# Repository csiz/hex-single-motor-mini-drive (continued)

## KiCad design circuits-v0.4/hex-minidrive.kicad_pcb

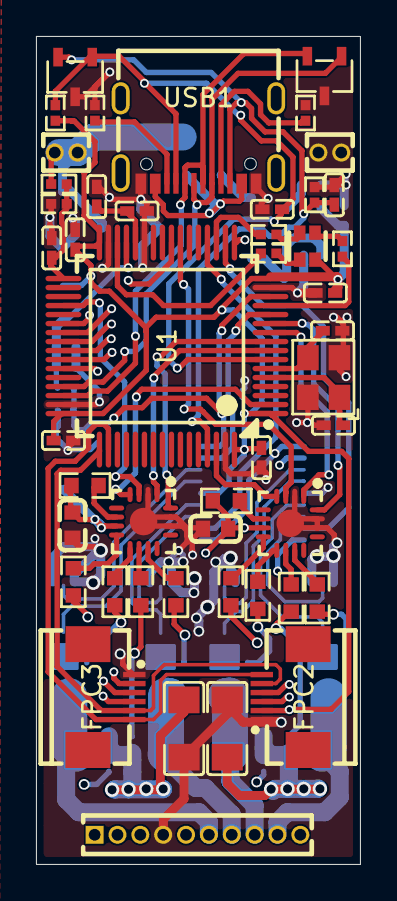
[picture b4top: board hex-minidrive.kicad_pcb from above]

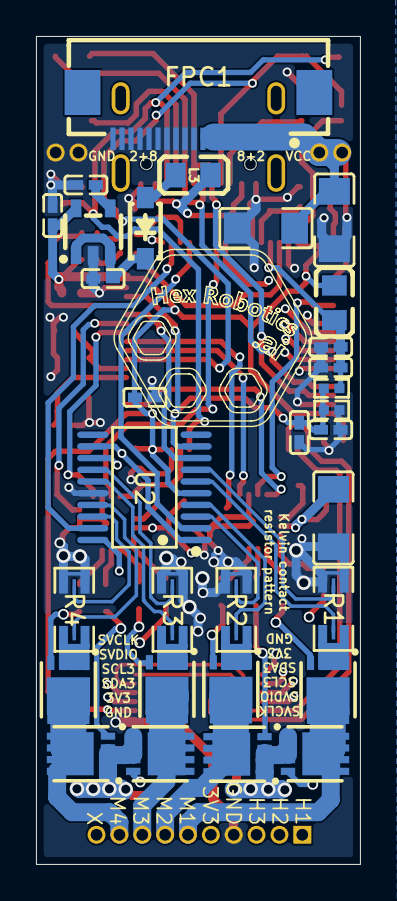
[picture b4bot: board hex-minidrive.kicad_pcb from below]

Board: 4 copper layers, 18.0 x 46.0 mm, 78 parts (31 on the bottom side), 80 nets.

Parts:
C0, C1, C2, C3, C4: 10uF; C1206
C21, C101, C106, C108, C109, C110, C111, C112, C113, C114: 100nF; C0402
C31, C32, C102, C105, C107: 1uF; C0402
C33: 10nF; C0402
C103, C104: 15pF; C0402
C115: 1nF; C0402
C501, C601: 100nF; C0603
D1: SOD-123_L2.7-W1.6-LS3.7-RD-1
D2, D3: SOT-23-3_L3.0-W1.7-P0.95-LS2.9-BR
FPC1: FPC-SMD_20P-P0.50_XUNPU_FPC-05F-20PH20
FPC2, FPC3: FPC-SMD_6P-P0.50_XUNPU_FPC-05F-6PH20
H1: 10P 1.27mm header; HDR-TH_HX-PZ1.27-1X10P-ZZ
H2, H3: 2P-1.27mm-header; HDR-TH_2P-P1.27-V-M-2
L2: 10uH; L0805
L3: 300mΩ; L0805
LED1: LED-ARRAY-SMD_4P-L1.6-W1.5-BR_XL-1615RGBC-RF
Q1, Q3, Q5, Q7: DFN-8_L3.0-W3.0-P0.65-BL-MOSFET_shifted
Q2, Q4, Q6, Q8: DFN-8_L3.0-W3.0-P0.65-BL-MOSFET
R1, R2, R3, R4: 10mΩ; R1206 Shunt with Kelvin connections
R5, R6: 5.1kΩ; R0402
R11, R12, R13, R14, R19: 10kΩ; R0402
R15, R16, R17: 1.5kΩ; R0402
R18: 100kΩ; R0402
R101, R102, R201, R202, R301, R302, R401, R402: 4.7Ω; R0603
R501, R601: 10Ω; R0603
U1: LQFP-64_L10.0-W10.0-P0.50-LS12.0-BL
U2: TSSOP-20_L6.5-W4.4-P0.65-LS6.4-BL
U3: SOT-23-5_L3.0-W1.6-P0.95-LS2.8-BL
U5, U6: QFN-16_L3.0-W3.0-P0.50-TL-EP1.7
USB1: USB-C-SMD_TYPE-C16PIN
X1: 16MHz; OSC-SMD_4P-L3.2-W2.5-BL

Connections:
3V3: C21.2, C32.2, C109.2, C111.2, C112.2, C113.2, FPC2.2, FPC3.2, H1.5, L2.1, LED1.2 (COM+), R14.1, U1.1 (VBAT), U1.16 (VDD), U1.32 (VDD), U1.48 (VDD), U1.64 (VDD), U2.5 (VS), U3.5 (OUT)
3V3A: C101.2, C102.2, L2.2, R13.2, U1.29 (VDDA)
5V: C31.2, D1.1 (-), U3.1 (IN), U3.3 (EN)
+Probe-1: R1.3 (Probe-1), U2.6 (IN+2)
+Probe-2: R2.3 (Probe-1), U2.4 (IN+1)
+Probe-3: R3.3 (Probe-1), U2.15 (IN+3)
+Probe-4: R4.3 (Probe-1), U2.17 (IN+4)
-Probe-1: R1.4 (Probe-2), U2.7 (IN±2)
-Probe-2: R2.4 (Probe-2), U2.3 (IN±1)
-Probe-3: R3.4 (Probe-2), U2.14 (IN±3)
-Probe-4: R4.4 (Probe-2), U2.18 (IN±4)
/Blue-LED: LED1.3 (B-), R16.1
/Driver1-internal-LDO: R501.2, U5.6 (VCC1)
/Driver2-internal-LDO: R601.2, U6.6 (VCC1)
/Gate-1-Negative: Q1.2 (G), R101.2
/Gate-1-Positive: Q2.2 (G), R102.1
/Gate-2-Negative: Q3.2 (G), R201.2
/Gate-2-Positive: Q4.2 (G), R202.1
/Gate-3-Negative: Q5.2 (G), R301.2
/Gate-3-Positive: Q6.2 (G), R302.1
/Gate-4-Negative: Q7.2 (G), R401.2
/Gate-4-Positive: Q8.2 (G), R402.1
/Green-LED: LED1.4 (G-), R15.1
/LDO-Bypass-Capacitor: C33.2, U3.4 (BYP)
/OSC1: C103.2, U1.5 (PF0-OSC_IN), X1.1 (OSC1)
/OSC2: C104.2, U1.6 (PF1-OSC_OUT), X1.3 (OSC2)
/Red-LED: LED1.1 (R-), R17.2
/Shunt-1: Q1.1 (S), R1.1 (Shunt-1)
/Shunt-2: Q3.1 (S), R2.1 (Shunt-1)
/Shunt-3: Q5.1 (S), R3.1 (Shunt-1)
/Shunt-4: Q7.1 (S), R4.1 (Shunt-1)
/USB:5V: L3.1, USB1.A4B9 (VBUS), USB1.B4A9 (VBUS)
/USB:5V-filtered: D1.2 (+), L3.2
/USB:CC1: R6.2, USB1.A5 (CC1)
/USB:CC2: R5.2, USB1.B5 (CC2)
ADC1_IN1/M1_CURRENT: U1.12 (PA0), U2.8 (OUT2)
ADC1_IN3/HALF_VREF: C107.2, C108.2, R12.2, R13.1, U1.14 (PA2), U2.1 (REF1), U2.9 (REF2), U2.12 (REF3), U2.20 (REF4)
ADC1_IN4/M3_CURRENT: U1.17 (PA3), U2.13 (OUT3)
ADC2_IN3/M2_CURRENT: U1.20 (PA6), U2.2 (OUT1)
ADC2_IN14/VOLTAGE: C115.2, R18.1, R19.2, U1.33 (PB11)
ADC2_IN17/M4_CURRENT: U1.18 (PA4), U2.19 (OUT4)
BOOT0/STOP: C114.2, D3.2 (A1), R11.2, U1.61 (PB8-BOOT0), USB1.B8 (SBU2)
GND: C0.1, C1.1, C2.1, C3.1, C4.1, C21.1, C31.1, C32.1, C33.1, C101.1, C102.1, C103.1, C104.1, C105.1, C106.1, C107.1, C108.1, C109.1, C110.1, C111.1, C112.1, C113.1, C114.1, C115.1, C501.1, C601.1, D2.3 (K), D3.3 (K), FPC1.11, FPC1.12, FPC1.13, FPC1.14, FPC1.15, FPC1.16, FPC1.17, FPC1.18, FPC1.19, FPC1.20, FPC2.1, FPC3.1, H1.4, H2.1, H2.2, R1.2 (Shunt-2), R2.2 (Shunt-2), R3.2 (Shunt-2), R4.2 (Shunt-2), R5.1, R6.1, R11.1, R12.1, R19.1, U1.15 (VSS), U1.27 (VSSA), U1.31 (VSS), U1.47 (VSS), U1.63 (VSS), U2.16 (GND), U3.2 (GND), U5.2 (LIN3), U5.14 (GND), U5.15 (HIN3), U5.17 (EP), U6.2 (LIN3), U6.14 (GND), U6.15 (HIN3), U6.17 (EP), USB1.A1B12 (GND), USB1.B1A12 (GND), X1.2 (GND), X1.4 (GND)
I2C2_SCL: FPC2.4, U1.43 (PA9)
I2C2_SDA: FPC2.3, U1.42 (PA8)
I2C3_SCL: FPC3.4, U1.40 (PC8)
I2C3_SDA: FPC3.3, U1.41 (PC9)
M1: H1.6, Q1.3 (D), Q2.3 (D)
M2: H1.7, Q3.3 (D), Q4.3 (D)
M3: H1.8, Q5.3 (D), Q6.3 (D)
M4: H1.9, Q7.3 (D), Q8.3 (D)
N-Gate-1: R101.1, U5.9 (LO1)
N-Gate-2: R201.1, U5.11 (LO2)
N-Gate-3: R301.1, U6.9 (LO1)
N-Gate-4: R401.1, U6.11 (LO2)
NRST: C110.2, D3.1 (A1), R14.2, U1.7 (PG10-NRST), USB1.A8 (SBU1)
P-Gate-1: R102.2, U5.8 (HO1)
P-Gate-2: R202.2, U5.10 (HO2)
P-Gate-3: R302.2, U6.8 (HO1)
P-Gate-4: R402.2, U6.10 (HO2)
SYS_JTCK-SWCLK: FPC2.6, FPC3.6, U1.50 (PA14)
SYS_JTMS-SVDIO: FPC2.5, FPC3.5, U1.49 (PA13)
TIM1_CH1: U1.8 (PC0), U5.1 (HIN1)
TIM1_CH1N: U1.2 (PC13), U5.4 (LIN1)
TIM1_CH2: U1.9 (PC1), U5.16 (HIN2)
TIM1_CH2N: U1.36 (PB14), U5.3 (LIN2)
TIM1_CH3: U1.10 (PC2), U6.1 (HIN1)
TIM1_CH3N: U1.62 (PB9), U6.4 (LIN1)
TIM1_CH4: U1.11 (PC3), U6.16 (HIN2)
TIM1_CH4N: U1.23 (PC5), U6.3 (LIN2)
TIM2_CH1/GREEN_LED: R15.2, U1.19 (PA5)
TIM2_CH2/BLUE_LED: R16.2, U1.13 (PA1)
TIM2_CH3/RED_LED: R17.1, U1.30 (PB10)
TIM3_CH1/ENCODER_1: H1.1, U1.38 (PC6)
TIM3_CH2/ENCODER_2: H1.2, U1.39 (PC7)
TIM3_CH3/ENCODER_3: H1.3, U1.24 (PB0)
USB_D_N: D2.1 (A1), U1.45 (PA11), USB1.A7 (DN1), USB1.B7 (DN2)
USB_D_P: D2.2 (A1), U1.46 (PA12), USB1.A6 (DP1), USB1.B6 (DP2)
VCC: C0.2, C1.2, C2.2, C3.2, C4.2, C501.2, C601.2, FPC1.1, FPC1.2, FPC1.3, FPC1.4, FPC1.5, FPC1.6, FPC1.7, FPC1.8, FPC1.9, FPC1.10, H3.1, H3.2, Q2.1 (S), Q4.1 (S), Q6.1 (S), Q8.1 (S), R18.2, R501.1, R601.1, U5.7 (VCC2), U6.7 (VCC2)
VREF: C105.2, C106.2, U1.28 (VREF+)

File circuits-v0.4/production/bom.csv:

Designator,Footprint,Quantity,Value,LCSC Part #
"C0, C1, C2, C3, C4",C1206,5,10uF,C13585
"C101, C106, C108, C109, C110, C111, C112, C113, C114, C21",C0402,10,100nF,C307331
"C102, C105, C107, C31, C32",C0402,5,1uF,C52923
"C103, C104",C0402,2,15pF,C1548
C115,C0402,1,1nF,C1523
C33,C0402,1,10nF,C15195
"C501, C601",C0603,2,100nF,C14663
D1,SOD-123_L2.7-W1.6-LS3.7-RD-1,1,~,C8598
"D2, D3",SOT-23-3_L3.0-W1.7-P0.95-LS2.9-BR,2,~,C32677
FPC1,FPC-SMD_20P-P0.50_XUNPU_FPC-05F-20PH20,1,~,C2856803
"FPC2, FPC3",FPC-SMD_6P-P0.50_XUNPU_FPC-05F-6PH20,2,~,C2856796
L2,L0805,1,10uH,C1046
L3,L0805,1,300mΩ,C1017
LED1,LED-ARRAY-SMD_4P-L1.6-W1.5-BR_XL-1615RGBC-RF,1,~,C965840
"Q1, Q3, Q5, Q7",DFN-8_L3.0-W3.0-P0.65-BL-MOSFET_shifted,4,~,C315567
"Q2, Q4, Q6, Q8",DFN-8_L3.0-W3.0-P0.65-BL-MOSFET,4,~,C541711
"R1, R2, R3, R4",R1206 Shunt with Kelvin connections,4,10mΩ,C7467248
"R101, R102, R201, R202, R301, R302, R401, R402",R0603,8,4.7Ω,C23164
"R11, R12, R13, R14, R19",R0402,5,10kΩ,C25744
"R15, R16, R17",R0402,3,1.5kΩ,C25867
R18,R0402,1,100kΩ,C25741
"R5, R6",R0402,2,5.1kΩ,C25905
"R501, R601",R0603,2,10Ω,C22859
U1,LQFP-64_L10.0-W10.0-P0.50-LS12.0-BL,1,~,C431633
U2,TSSOP-20_L6.5-W4.4-P0.65-LS6.4-BL,1,~,C2058366
U3,SOT-23-5_L3.0-W1.6-P0.95-LS2.8-BL,1,~,C2969807
"U5, U6",QFN-16_L3.0-W3.0-P0.50-TL-EP1.7,2,~,C20416138
USB1,USB-C-SMD_TYPE-C16PIN,1,~,C393939
X1,OSC-SMD_4P-L3.2-W2.5-BL,1,16MHz,C13738

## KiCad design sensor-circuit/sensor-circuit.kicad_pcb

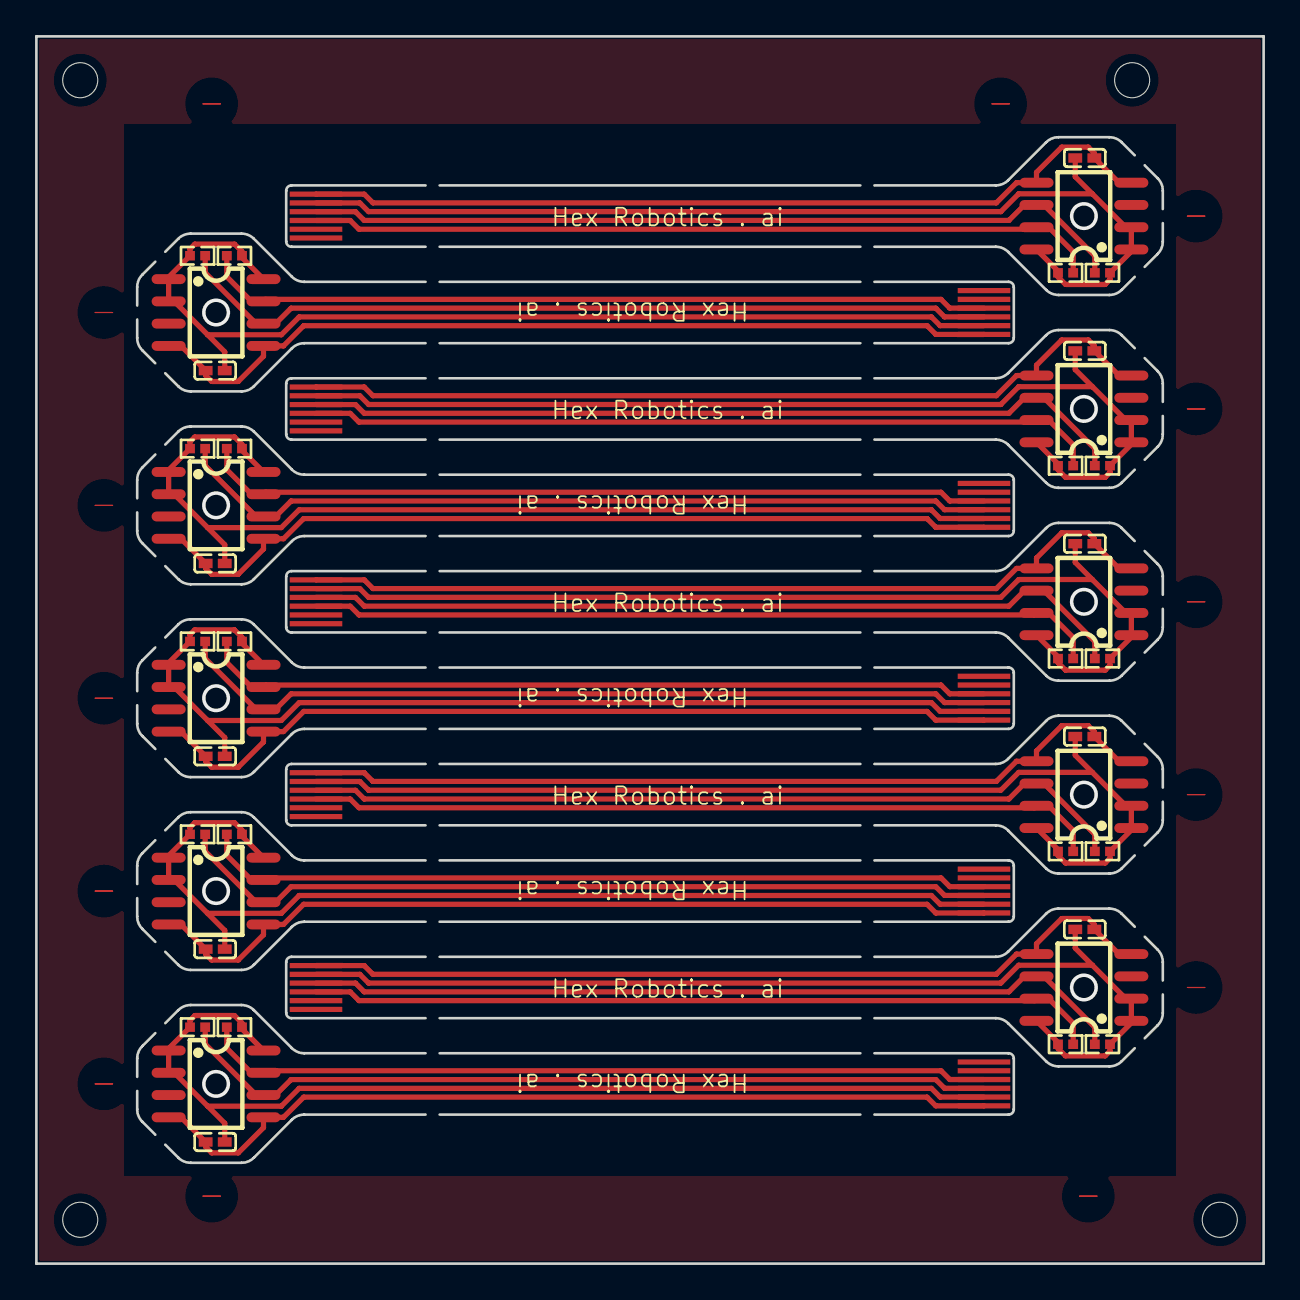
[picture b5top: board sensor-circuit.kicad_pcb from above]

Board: 2 copper layers, 70.0 x 70.0 mm, 50 parts (0 on the bottom side), 40 nets.

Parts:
C1, C2, C3, C4, C5, C6, C7, C8, C9, C10: 100nF; C0402
FPC1, FPC2, FPC3, FPC4, FPC5, FPC6, FPC7, FPC8, FPC9, FPC10: FPC-6P-P0.50-Pattern
R1, R2, R3, R4, R5, R6, R7, R8, R9, R10, R11, R12, R13, R14, R15, R16, R17, R18, R19, R20: 10kΩ; R0402
U1, U2, U3, U4, U5, U6, U7, U8, U9, U10: SOIC-8_L5.0-W4.0-P1.27-LS6.0-BL

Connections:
/sensor-circuit-singlet1/3V3: C2.2, FPC2.5, R3.2, R4.2, U2.1 (VDD5V), U2.2 (VDD3V3), U2.8 (DIR)
/sensor-circuit-singlet1/GND: C2.1, FPC2.6, U2.4 (GND), U2.5 (PGO)
/sensor-circuit-singlet1/SCL: FPC2.3, R3.1, U2.7 (SCL)
/sensor-circuit-singlet1/SDA: FPC2.4, R4.1, U2.6 (SDA)
/sensor-circuit-singlet2/3V3: C3.2, FPC3.5, R5.2, R6.2, U3.1 (VDD5V), U3.2 (VDD3V3), U3.8 (DIR)
/sensor-circuit-singlet2/GND: C3.1, FPC3.6, U3.4 (GND), U3.5 (PGO)
/sensor-circuit-singlet2/SCL: FPC3.3, R5.1, U3.7 (SCL)
/sensor-circuit-singlet2/SDA: FPC3.4, R6.1, U3.6 (SDA)
/sensor-circuit-singlet3/3V3: C4.2, FPC4.5, R7.2, R8.2, U4.1 (VDD5V), U4.2 (VDD3V3), U4.8 (DIR)
/sensor-circuit-singlet3/GND: C4.1, FPC4.6, U4.4 (GND), U4.5 (PGO)
/sensor-circuit-singlet3/SCL: FPC4.3, R7.1, U4.7 (SCL)
/sensor-circuit-singlet3/SDA: FPC4.4, R8.1, U4.6 (SDA)
/sensor-circuit-singlet4/3V3: C5.2, FPC5.5, R9.2, R10.2, U5.1 (VDD5V), U5.2 (VDD3V3), U5.8 (DIR)
/sensor-circuit-singlet4/GND: C5.1, FPC5.6, U5.4 (GND), U5.5 (PGO)
/sensor-circuit-singlet4/SCL: FPC5.3, R9.1, U5.7 (SCL)
/sensor-circuit-singlet4/SDA: FPC5.4, R10.1, U5.6 (SDA)
/sensor-circuit-singlet5/3V3: C6.2, FPC6.5, R11.2, R12.2, U6.1 (VDD5V), U6.2 (VDD3V3), U6.8 (DIR)
/sensor-circuit-singlet5/GND: C6.1, FPC6.6, U6.4 (GND), U6.5 (PGO)
/sensor-circuit-singlet5/SCL: FPC6.3, R11.1, U6.7 (SCL)
/sensor-circuit-singlet5/SDA: FPC6.4, R12.1, U6.6 (SDA)
/sensor-circuit-singlet6/3V3: C7.2, FPC7.5, R13.2, R14.2, U7.1 (VDD5V), U7.2 (VDD3V3), U7.8 (DIR)
/sensor-circuit-singlet6/GND: C7.1, FPC7.6, U7.4 (GND), U7.5 (PGO)
/sensor-circuit-singlet6/SCL: FPC7.3, R13.1, U7.7 (SCL)
/sensor-circuit-singlet6/SDA: FPC7.4, R14.1, U7.6 (SDA)
/sensor-circuit-singlet7/3V3: C8.2, FPC8.5, R15.2, R16.2, U8.1 (VDD5V), U8.2 (VDD3V3), U8.8 (DIR)
/sensor-circuit-singlet7/GND: C8.1, FPC8.6, U8.4 (GND), U8.5 (PGO)
/sensor-circuit-singlet7/SCL: FPC8.3, R15.1, U8.7 (SCL)
/sensor-circuit-singlet7/SDA: FPC8.4, R16.1, U8.6 (SDA)
/sensor-circuit-singlet8/3V3: C9.2, FPC9.5, R17.2, R18.2, U9.1 (VDD5V), U9.2 (VDD3V3), U9.8 (DIR)
/sensor-circuit-singlet8/GND: C9.1, FPC9.6, U9.4 (GND), U9.5 (PGO)
/sensor-circuit-singlet8/SCL: FPC9.3, R17.1, U9.7 (SCL)
/sensor-circuit-singlet8/SDA: FPC9.4, R18.1, U9.6 (SDA)
/sensor-circuit-singlet9/3V3: C10.2, FPC10.5, R19.2, R20.2, U10.1 (VDD5V), U10.2 (VDD3V3), U10.8 (DIR)
/sensor-circuit-singlet9/GND: C10.1, FPC10.6, U10.4 (GND), U10.5 (PGO)
/sensor-circuit-singlet9/SCL: FPC10.3, R19.1, U10.7 (SCL)
/sensor-circuit-singlet9/SDA: FPC10.4, R20.1, U10.6 (SDA)
/sensor-circuit-singlet/3V3: C1.2, FPC1.5, R1.2, R2.2, U1.1 (VDD5V), U1.2 (VDD3V3), U1.8 (DIR)
/sensor-circuit-singlet/GND: C1.1, FPC1.6, U1.4 (GND), U1.5 (PGO)
/sensor-circuit-singlet/SCL: FPC1.3, R1.1, U1.7 (SCL)
/sensor-circuit-singlet/SDA: FPC1.4, R2.1, U1.6 (SDA)

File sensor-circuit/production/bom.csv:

Designator,Footprint,Quantity,Value,LCSC Part #
"C1, C10, C2, C3, C4, C5, C6, C7, C8, C9",C0402,10,100nF,C60474
"R1, R10, R11, R12, R13, R14, R15, R16, R17, R18, R19, R2, R20, R3, R4, R5, R6, R7, R8, R9",R0402,20,10kΩ,C25744
"U1, U10, U2, U3, U4, U5, U6, U7, U8, U9",SOIC-8_L5.0-W4.0-P1.27-LS6.0-BL,10,~,C499458
